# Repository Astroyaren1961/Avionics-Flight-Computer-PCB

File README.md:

# Rocket Avionics Flight Computer PCB (STM32F407)

A custom 2-layer prototype Printed Circuit Board (PCB) designed in **KiCad** for competitive rocketry avionics and telemetry applications (TEKNOFEST Rocket Competition).

## Status

- Revision A, design complete
- ERC: 0 errors, 0 warnings
- DRC (including schematic parity check): 0 errors, 0 warnings
- Gerber and drill files generated (see `Avionics_Flight_Computer_gerber.zip`)
- Not yet fabricated or tested

## Overview

This board serves as the central flight computer and sensor hub, integrating onboard inertial and barometric sensors with dedicated hardware communication interfaces for external GPS, high-g accelerometer, and long-range wireless telemetry modules.

## Board at a Glance

| Item | Value |
|---|---|
| Size | 109.5 x 72.5 mm |
| Layers | 2 (F.Cu / B.Cu), solid GND copper pour on both sides |
| Thickness | 1.6 mm |
| Mounting | 4 x M3 holes (3.2 mm) near the corners |
| Design tool | KiCad 10.0 |

## Hardware Architecture & Key Components

- **Microcontroller:** STMicroelectronics **STM32F407VGTx** (ARM Cortex-M4, LQFP-100) with 8 MHz crystal, decoupling capacitors and VCAP network. BOOT0 is tied to GND (boots from flash).
- **Power Management:** power enters through J4.
  - **D2 (SS34):** reverse-polarity protection
  - **D3 (SMBJ15A):** TVS diode for voltage spikes
  - **C2 (100 uF / 35 V):** input capacitor
  - **LM2596S-3.3:** step-down regulator, with L1 (33 uH), Schottky catch diode D1 and output capacitor C1 (220 uF), providing a **3.3 V** rail.
  - The SMBJ15A has a 15 V standoff voltage, so the input must stay below 15 V. The design target is a 2S-3S LiPo class supply (about 7-12.6 V).
- **Onboard Sensors (I2C1 bus with 4.7 kOhm pull-ups):**
  - **BNO055:** 9-axis absolute orientation IMU (LGA-28), COM3 tied to GND (I2C address 0x28)
  - **MS5611-01BA:** barometric pressure and altitude sensor (LGA-8), CSB tied to GND (I2C address 0x77)
- **External Module Interfaces:**
  - **SPI1 Header (J1):** external high-g accelerometer (**H3LIS331DL**) or flash memory
  - **UART2 Header (J2):** **NEO-8M** GPS module
  - **UART3 Header (J3):** **E220-400T30D** LoRa wireless telemetry transceiver
- **Programming / Debug:** SWD header (J5). NRST has a 10 kOhm pull-up and a 100 nF capacitor.
- **PCB Layout:** 2-layer stack-up with dual-sided solid GND pours. The VIN / switch-node power path uses 0.6 mm traces; signal traces are 0.2-0.25 mm.

## Connector Pinout

| Connector | Pin 1 | Pin 2 | Pin 3 | Pin 4 | Pin 5 | Pin 6 | Pin 7 | Pin 8 |
|---|---|---|---|---|---|---|---|---|
| **J1** (SPI1) | 3.3V | GND | SPI1_SCK | SPI1_MOSI | SPI1_MISO | SPI1_CS | not connected | not connected |
| **J2** (UART2) | 3.3V | GND | UART2_RX | UART2_TX | | | | |
| **J3** (UART3) | GND | GND | UART3_TX | UART3_RX | 3.3V | GND | | |
| **J4** (power in) | VIN+ (via D2) | GND | | | | | | |
| **J5** (SWD) | 3.3V | SWDIO | SWCLK | GND | | | | |

UART directions are named from the STM32 side (UART2_TX is the MCU transmit line).

## MCU Pin Assignments

| Function | MCU pin |
|---|---|
| I2C1 SCL / SDA | PB6 / PB7 |
| SPI1 CS / SCK / MISO / MOSI | PA4 / PA5 / PA6 / PA7 |
| UART2 TX / RX | PA2 / PA3 |
| UART3 TX / RX | PB10 / PB11 |
| SWDIO / SWCLK | PA13 / PA14 |

## Renders

| Top | Bottom |
|---|---|
|  |  |

## Repository Contents

- `Avionics_Flight_Computer_PCB.kicad_pro` - KiCad project file
- `Avionics_Flight_Computer_PCB.kicad_sch` - complete circuit schematic
- `Avionics_Flight_Computer_PCB.kicad_pcb` - 2-layer PCB layout
- `Avionics_Flight_Computer_PCB.pdf` - schematic in PDF form
- `Avionics_Flight_Computer_gerber.zip` - Gerber and drill files for fabrication
- `pcb_top.png`, `pcb_bottom.png`, `pcb_angle.png` - 3D renders

## Known Limitations (ideas for the next revision)

1. Decoupling capacitors C9 and C10 sit about 8 mm from the sensor supply pins, and C14 and C15 are not directly next to the MCU supply pins. Placement was limited by routing density.
2. The BNO055 RESET and INT pins are not connected, so the IMU can only be reset by power cycling.
3. J1 has a single chip-select line (PA4), so an accelerometer and a flash chip cannot both be used on J1 at the same time.
4. J3 breaks out only UART, 3.3 V and GND. The E220 module's mode pins (M0/M1) and AUX are not connected to the MCU. Check the module's supply range and peak transmit current in its datasheet, since the board provides 3.3 V only.
5. The input capacitor C2 is 100 uF. The LM2596 datasheet's typical application uses a larger value, so it can be increased in a later revision.

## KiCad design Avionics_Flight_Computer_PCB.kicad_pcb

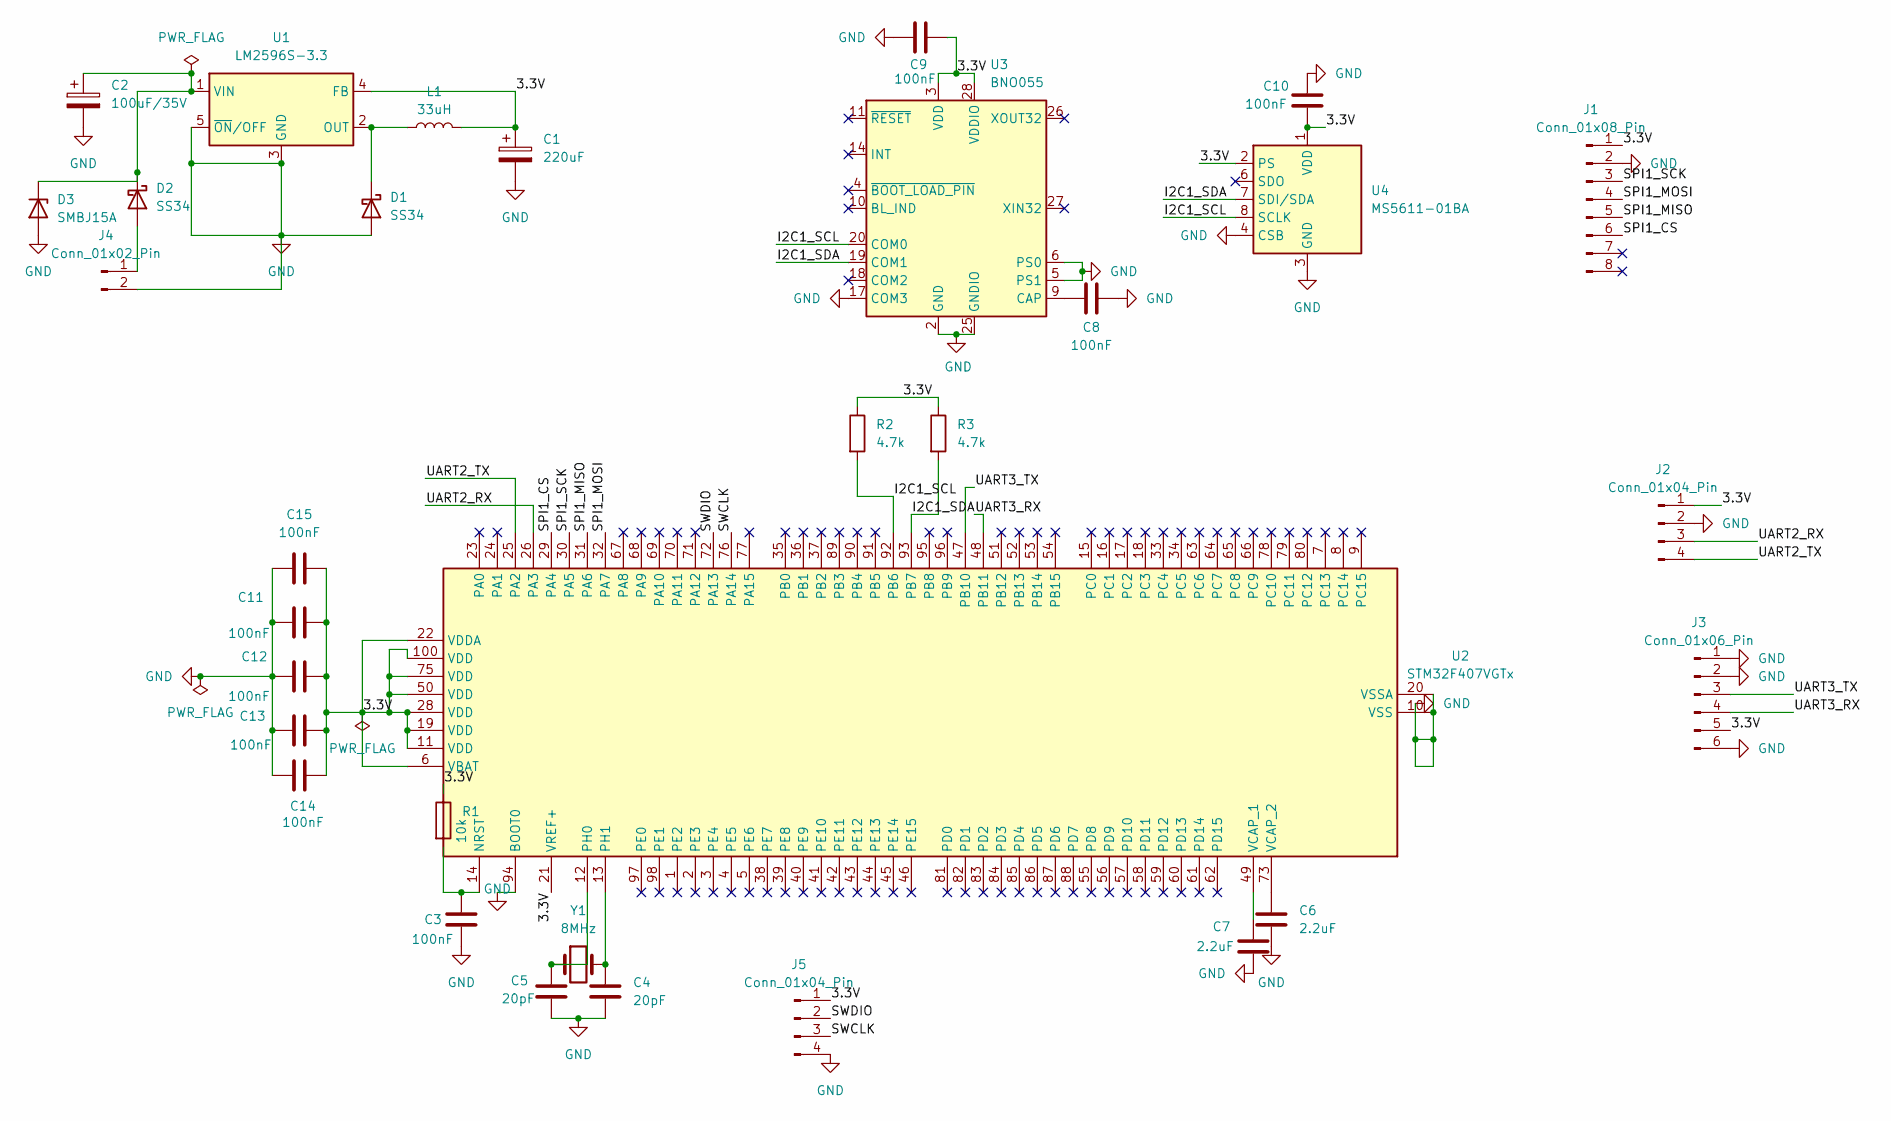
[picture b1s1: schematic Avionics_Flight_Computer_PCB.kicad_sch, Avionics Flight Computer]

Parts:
C1: 220uF; CP_Radial_D8.0mm_P3.50mm
C2: 100uF/35V; CP_Radial_D10.0mm_P5.00mm
C3, C8, C9, C10, C11, C12, C13, C14, C15: 100nF; C_0805_2012Metric
C4, C5: 20pF; C_0805_2012Metric
C6, C7: 2.2uF; C_0805_2012Metric
D1, D2: SS34; D_SMA
D3: SMBJ15A; D_SMB
J1: Conn_01x08_Pin; PinHeader_1x08_P2.54mm_Vertical
J2, J5: Conn_01x04_Pin; PinHeader_1x04_P2.54mm_Vertical
J3: Conn_01x06_Pin; PinHeader_1x06_P2.54mm_Vertical
J4: Conn_01x02_Pin; PinHeader_1x02_P2.54mm_Vertical
L1: 33uH; L_Bourns_SRR1260
R1: 10k; R_0805_2012Metric
R2, R3: 4.7k; R_0805_2012Metric
U1: LM2596S-3.3; TO-263-5_TabPin3
U2: STM32F407VGTx; LQFP-100_14x14mm_P0.5mm
U3: BNO055; LGA-28_5.2x3.8mm_P0.5mm
U4: MS5611-01BA; LGA-8_3x5mm_P1.25mm
Y1: 8MHz; Crystal_HC49-U_Vertical

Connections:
/3.3V: C1.1, C9.2, C10.2, C11.2, C12.2, C13.1, C14.2, C15.2, J1.1, J2.1, J3.5, J5.1, L1.2, R1.1, R2.1, R3.1, U1.4 (FB), U2.6 (VBAT), U2.11 (VDD), U2.19 (VDD), U2.21 (VREF+), U2.22 (VDDA), U2.28 (VDD), U2.50 (VDD), U2.75 (VDD), U2.100 (VDD), U3.3 (VDD), U3.28 (VDDIO), U4.1 (VDD), U4.2 (PS)
/I2C1_SCL: R2.2, U2.92 (PB6), U3.20 (COM0), U4.8 (SCLK)
/I2C1_SDA: R3.2, U2.93 (PB7), U3.19 (COM1), U4.7 (SDI/SDA)
/SPI1_CS: J1.6, U2.29 (PA4)
/SPI1_MISO: J1.5, U2.31 (PA6)
/SPI1_MOSI: J1.4, U2.32 (PA7)
/SPI1_SCK: J1.3, U2.30 (PA5)
/SWCLK: J5.3, U2.76 (PA14)
/SWDIO: J5.2, U2.72 (PA13)
/UART2_RX: J2.3, U2.26 (PA3)
/UART2_TX: J2.4, U2.25 (PA2)
/UART3_RX: J3.4, U2.48 (PB11)
/UART3_TX: J3.3, U2.47 (PB10)
GND: C1.2, C2.2, C3.2, C4.2, C5.2, C6.1, C7.2, C8.2, C9.1, C10.1, C11.1, C12.1, C13.2, C14.1, C15.1, D1.2 (A), D3.2 (A), J1.2, J2.2, J3.1, J3.2, J3.6, J4.2, J5.4, U1.3 (GND), U1.5 (~ON/OFF), U2.10 (VSS), U2.20 (VSSA), U2.27 (VSS), U2.74 (VSS), U2.94 (BOOT0), U2.99 (VSS), U3.2 (GND), U3.5 (PS1), U3.6 (PS0), U3.17 (COM3), U3.25 (GNDIO), U4.3 (GND), U4.4 (CSB), U4.5 (CSB)
unnamed: D1.1 (K), L1.1, U1.2 (OUT)
unnamed: D2.2 (A), J4.1
unnamed: C2.1, D2.1 (K), D3.1 (K), U1.1 (VIN)
unnamed: C3.1, R1.2, U2.14 (NRST)
unnamed: C5.1, U2.12 (PH0), Y1.1
unnamed: C4.1, U2.13 (PH1), Y1.2
unnamed: C7.1, U2.49 (VCAP_1)
unnamed: C6.2, U2.73 (VCAP_2)
unnamed: C8.1, U3.9 (CAP)

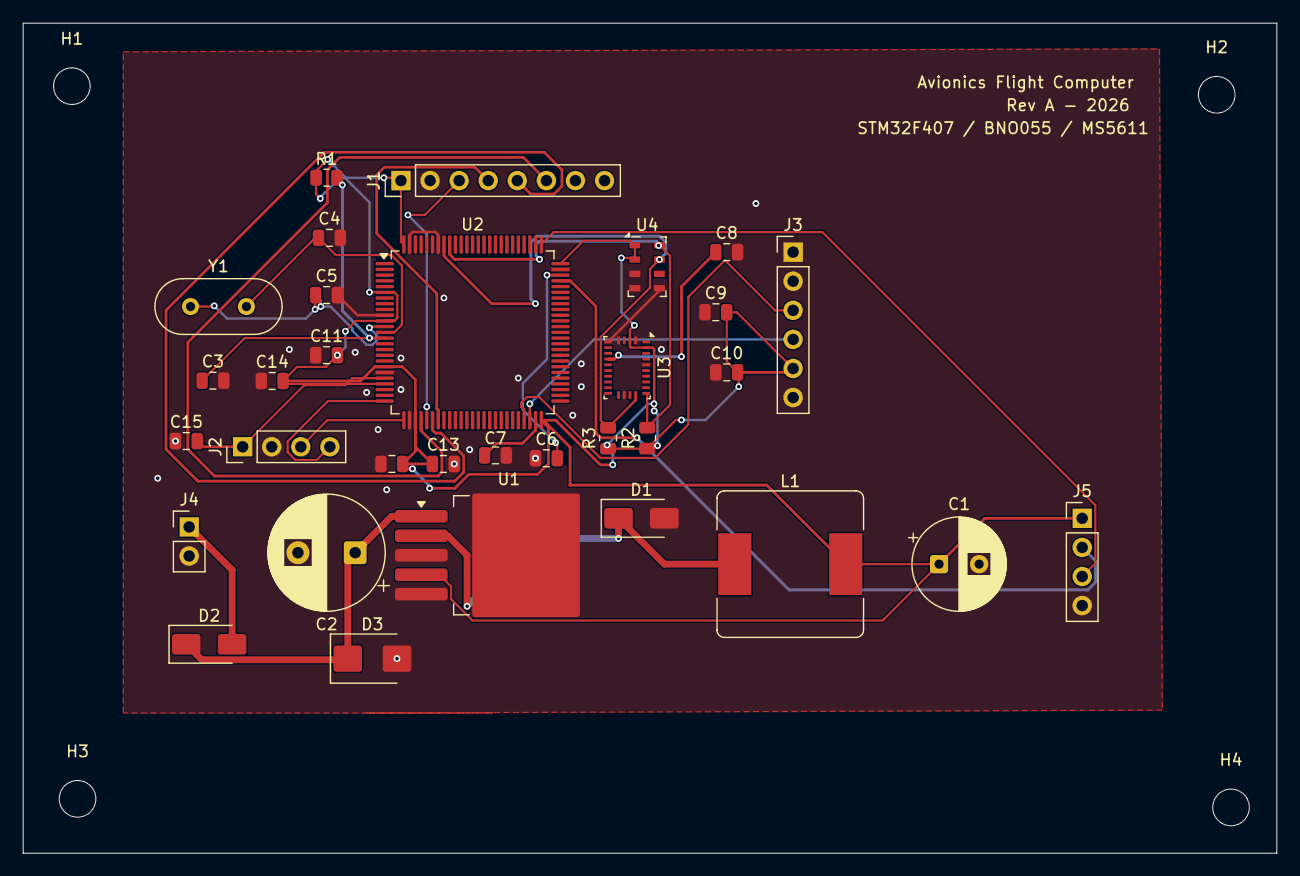
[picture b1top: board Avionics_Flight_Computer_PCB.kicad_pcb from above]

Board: 2 copper layers, 109.5 x 72.5 mm, 36 parts (0 on the bottom side), 23 nets.

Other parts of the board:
H1, H2, H3, H4: MountingHole_3.2mm_M3
